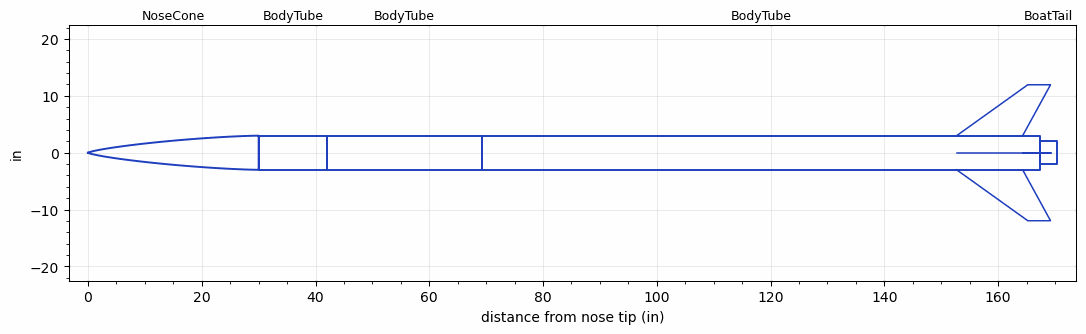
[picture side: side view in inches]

<RASAeroDocument>
 <FileVersion>2</FileVersion>
 <RocketDesign>
  <NoseCone>
   <Length>29.9999</Length>
   <Diameter>6</Diameter>
   <Shape>Von Karman Ogive</Shape>
   <Location>0</Location>
  </NoseCone>
  <BodyTube>
   <Length>12</Length>
   <Diameter>6</Diameter>
   <Location>29.9999</Location>
  </BodyTube>
  <BodyTube>
   <Length>27.2579</Length>
   <Diameter>6</Diameter>
   <Location>41.9999</Location>
  </BodyTube>
  <BodyTube>
   <Length>98.0598</Length>
   <Diameter>6</Diameter>
   <Location>69.2579</Location>
   <Fin>
    <Count>4</Count>
    <Chord>11.6</Chord>
    <Span>8.95</Span>
    <SweepDistance>12.5</SweepDistance>
    <TipChord>4</TipChord>
    <Thickness>0.3</Thickness>
    <Location>14.6</Location>
    <AirfoilSection>Subsonic NACA</AirfoilSection>
   </Fin>
  </BodyTube>
  <BoatTail>
   <Length>3</Length>
   <Diameter>4</Diameter>
   <RearDiameter>4</RearDiameter>
   <Location>167.3177</Location>
  </BoatTail>
  <Surface>Camouflage Paint</Surface>
  <CD>0</CD>
  <ModifiedBarrowman>False</ModifiedBarrowman>
  <Turbulence>False</Turbulence>
  <UseBooster1>False</UseBooster1>
  <UseBooster2>False</UseBooster2>
  <Comments>2027 IREC rocket Preliminary design - 10/08/2026</Comments>
 </RocketDesign>
 <LaunchSite>
  <Altitude>0</Altitude>
  <Pressure>27.0701</Pressure>
  <RodAngle>8</RodAngle>
  <RodLength>32.8</RodLength>
  <Temperature>76</Temperature>
  <WindSpeed>18</WindSpeed>
 </LaunchSite>
 <Recovery>
  <Altitude1>0</Altitude1>
  <Altitude2>0</Altitude2>
  <DeviceType1>None</DeviceType1>
  <DeviceType2>None</DeviceType2>
  <Event1>False</Event1>
  <Event2>False</Event2>
  <Size1>0</Size1>
  <Size2>0</Size2>
  <EventType1>None</EventType1>
  <EventType2>None</EventType2>
  <CD1>0</CD1>
  <CD2>0</CD2>
 </Recovery>
 <SimulationList>
  <Simulation>
   <SustainerLaunchWt>134.0265</SustainerLaunchWt>
   <SustainerCG>107.7841</SustainerCG>
   <SustainerIgnitionDelay>0</SustainerIgnitionDelay>
   <Booster1SeparationDelay>0</Booster1SeparationDelay>
   <Booster1IgnitionDelay>0</Booster1IgnitionDelay>
   <IncludeBooster1>False</IncludeBooster1>
   <Booster2Delay>0</Booster2Delay>
   <IncludeBooster2>False</IncludeBooster2>
  </Simulation>
  <Simulation>
   <SustainerLaunchWt>134.0265</SustainerLaunchWt>
   <SustainerCG>107.7841</SustainerCG>
   <SustainerIgnitionDelay>0</SustainerIgnitionDelay>
   <Booster1SeparationDelay>0</Booster1SeparationDelay>
   <Booster1IgnitionDelay>0</Booster1IgnitionDelay>
   <IncludeBooster1>False</IncludeBooster1>
   <Booster2Delay>0</Booster2Delay>
   <IncludeBooster2>False</IncludeBooster2>
  </Simulation>
  <Simulation>
   <SustainerLaunchWt>134.0265</SustainerLaunchWt>
   <SustainerCG>107.7841</SustainerCG>
   <SustainerIgnitionDelay>0</SustainerIgnitionDelay>
   <Booster1SeparationDelay>0</Booster1SeparationDelay>
   <Booster1IgnitionDelay>0</Booster1IgnitionDelay>
   <IncludeBooster1>False</IncludeBooster1>
   <Booster2Delay>0</Booster2Delay>
   <IncludeBooster2>False</IncludeBooster2>
  </Simulation>
  <Simulation>
   <SustainerLaunchWt>134.0265</SustainerLaunchWt>
   <SustainerCG>107.7841</SustainerCG>
   <SustainerIgnitionDelay>0</SustainerIgnitionDelay>
   <Booster1SeparationDelay>0</Booster1SeparationDelay>
   <Booster1IgnitionDelay>0</Booster1IgnitionDelay>
   <IncludeBooster1>False</IncludeBooster1>
   <Booster2Delay>0</Booster2Delay>
   <IncludeBooster2>False</IncludeBooster2>
  </Simulation>
 </SimulationList>
</RASAeroDocument>
